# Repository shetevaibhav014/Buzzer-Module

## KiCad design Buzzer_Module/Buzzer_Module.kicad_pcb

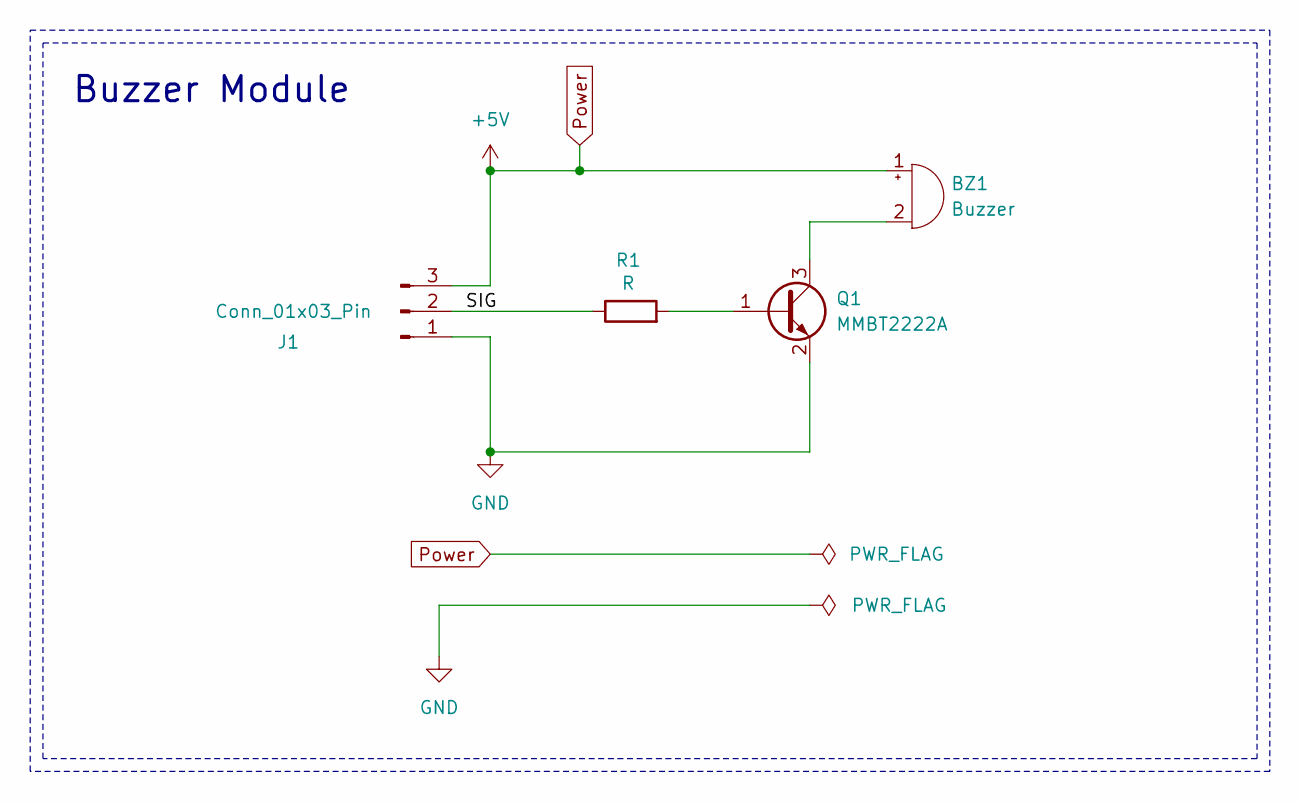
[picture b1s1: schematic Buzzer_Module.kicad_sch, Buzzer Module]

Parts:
BZ1: Buzzer; Buzzer_12x9.5RM7.6
J1: Conn_01x03_Pin; PinHeader_1x03_P2.54mm_Horizontal
Q1: MMBT2222A; SOT-23
R1: R; R_0603_1608Metric

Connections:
/SIG: J1.2, R1.1
GND: J1.1, Q1.2 (E)
unnamed: BZ1.2 (-), Q1.3 (C)
unnamed: Q1.1 (B), R1.2
Power: BZ1.1 (+), J1.3

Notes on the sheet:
Buzzer Module

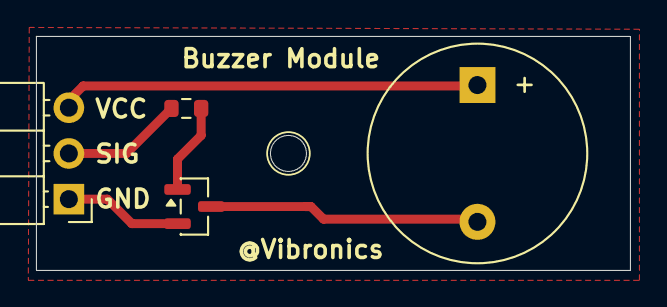
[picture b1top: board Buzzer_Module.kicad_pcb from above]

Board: 2 copper layers, 33.0 x 13.0 mm, 4 parts (0 on the bottom side), 5 nets.
